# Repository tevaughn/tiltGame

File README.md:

tiltGame
========

Open source hand held game device with two button and accelerometer controls

Result of final project for embedded system design class

Current code plays very simple maze game

link to video demo: http://youtu.be/vogIEGx5ChQ

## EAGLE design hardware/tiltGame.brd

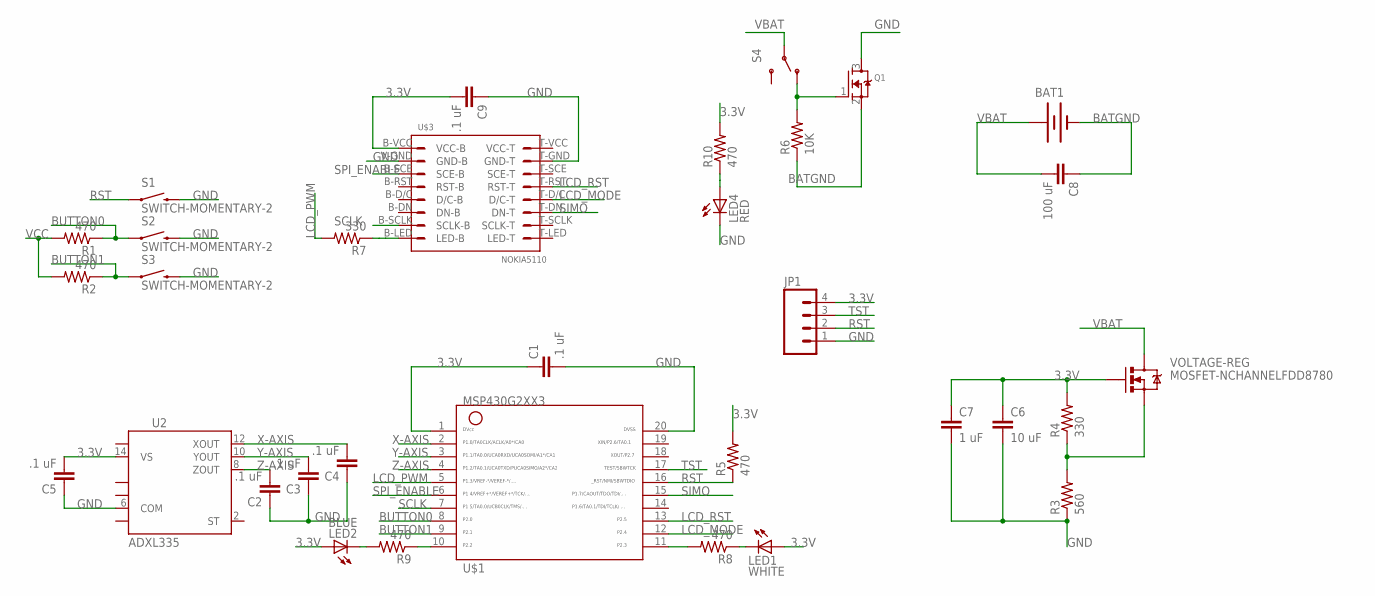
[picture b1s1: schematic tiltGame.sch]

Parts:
BAT1: BATTERY9V; BATTCON_9V
C1, C2, C3, C4, C5, C9: .1 uF; 0805
C6: 10 uF; 0805
C7: 1 uF; 0805
C8: 100 uF; 0805
JP1: M041X04_NO_SILK; 1X04_NO_SILK
LED1: WHITE; LED-1206
LED2: BLUE; LED-1206
LED4: RED; LED-1206
Q1: MOSFET-NWAVE; SOT23-W
R1, R2, R5, R8, R9, R10: 470; 0805
R3: 560; 0805
R4, R7: 330; 0805
R6: 10K; 0805
S1, S2, S3: SWITCH-MOMENTARY-2; TACTILE_PANISONIC
S4: SWITCH-SPDTPTH; SWITCH-SPDT
U2: ADXL335; LFCSP-16
U$1: MSP430G2XX3TSSOP; PW20
U$3: NOKIA5110
VOLTAGE-REG: MOSFET-NCHANNELFDD8780; DPAK

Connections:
3.3V: C1.1, C5.2, C6.1, C7.1, C9.2, JP1.4, LED1.A, LED2.A, R4.2, R5.2, R10.2, U2.14 (VS), U$1.1, U$3.B-VCC (VCC-B), VOLTAGE-REG.3 (G-3)
BATGND: BAT1.-, C8.1, Q1.2 (S), R6.1
BUTTON0: R1.1, S2.1, U$1.8
BUTTON1: R2.1, S3.1, U$1.9
GND: C1.2, C2.1, C3.1, C4.1, C5.1, C6.2, C7.2, C9.1, JP1.1, LED4.C, Q1.3 (D), R3.1, S1.2, S2.2, S3.2, U2.6 (COM), U$1.20, U$3.T-GND (GND-T), U$3.V-GND (GND-B)
LCD_MODE: U$1.12, U$3.T-D/C (D/C-T)
LCD_PWM: R7.2, U$1.5
LCD_RST: U$1.13, U$3.T-RST (RST-T)
unnamed: R3.2, R4.1, VOLTAGE-REG.1 (S-1)
unnamed: R7.1, U$3.B-LED (LED-B)
unnamed: R9.1, U$1.10
unnamed: R8.2, U$1.11
unnamed: LED4.A, R10.1
unnamed: LED1.C, R8.1
unnamed: LED2.C, R9.2
unnamed: Q1.1 (G), R6.2, S4.1 (O)
RST: JP1.2, R5.1, S1.1, U$1.16
SCLK: U$1.7, U$3.B-SCLK (SCLK-B)
SIMO: U$1.15, U$3.T-DN (DN-T)
SPI_ENABLE: U$1.6, U$3.B-SCE (SCE-B)
TST: JP1.3, U$1.17
VBAT: BAT1.+, C8.2, S4.2, VOLTAGE-REG.2 (D-2)
VCC: R1.2, R2.2
X-AXIS: C4.2, U2.12 (XOUT), U$1.2
Y-AXIS: C3.2, U2.10 (YOUT), U$1.3
Z-AXIS: C2.2, U2.8 (ZOUT), U$1.4

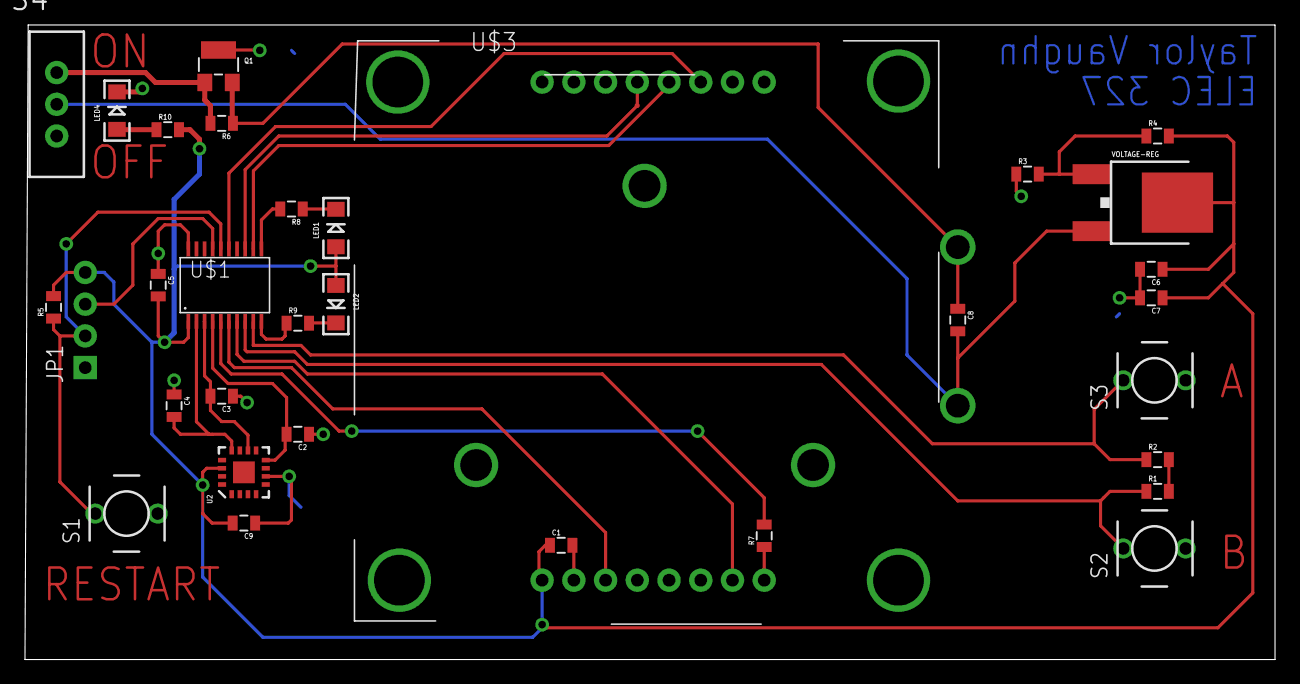
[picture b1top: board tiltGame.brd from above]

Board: 2 copper layers, 100.1 x 50.8 mm, 33 parts (1 on the bottom side), 26 nets.

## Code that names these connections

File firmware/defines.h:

#include <msp430.h>
#include "stdint.h"

/*
 * defines.h
 *
 *  Created on: Apr 1, 2014
 *      Author: Taylor
 */

#ifndef DEFINES_H_
#define DEFINES_H_

/* Port 2 */
#define BUTTON_A	BIT0
#define BUTTON_B	BIT1
#define LED_WHITE	BIT2
#define LED_BLUE	BIT3

#define LCD_MODE	BIT4
#define LCD_RST		BIT5

/* Port 1 */
#define XAXIS	BIT0
#define YAXIS	BIT1
#define ZAXIS	BIT2

#define LCD_PWM		BIT3
#define SPI_ENABLE	BIT4
#define CLOCK		BIT5
#define SIMO		BIT7


#define SECOND			0x2EE0 		// VLO runs at 12KHz
#define HALFSECOND		(SECOND >> 1)
#define QUARTERSECOND	(SECOND >> 2) // VLO runs at 12KHz
#define EIGHTSECOND		(SECOND >> 3) // VLO runs at 12KHz
#define SIXTEENTHSECOND (SECOND >> 4) // VLO runs at 12KHz

#define RIGHT	2
#define LEFT	3
#define DOWN	1
#define UP		0

#define HORZ_MAX	15
#define VERT_MAX	9

#define BLOCK_MAX 	5
#define COLUMN_MAX	77

// function prototypes
void buttonsConfig(void);
void configADC10(void);
void configTimerA0(void);
void configLCD(void);
void writeStringToLCD(const char *string);
void writeCharToLCD(char c);
void writeBlockToLCD(char *byte, unsigned char length);
void writeGraphicToLCD(char *byte, unsigned char transform);
void writeToLCD(unsigned char dataCommand, unsigned char data);
void clearLCD();
void clearBank(unsigned char bank);
void setAddr(unsigned char xAddr, unsigned char yAddr);
void initLCD();
void mazeInit(void);
void updateLocation(int);




#endif /* DEFINES_H_ */

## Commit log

2015-01-04 Added all hardware and software files
2015-01-05 updated README.md with video link
